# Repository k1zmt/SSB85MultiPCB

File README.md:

# SSB85MultiPCB

Watch it in the work here

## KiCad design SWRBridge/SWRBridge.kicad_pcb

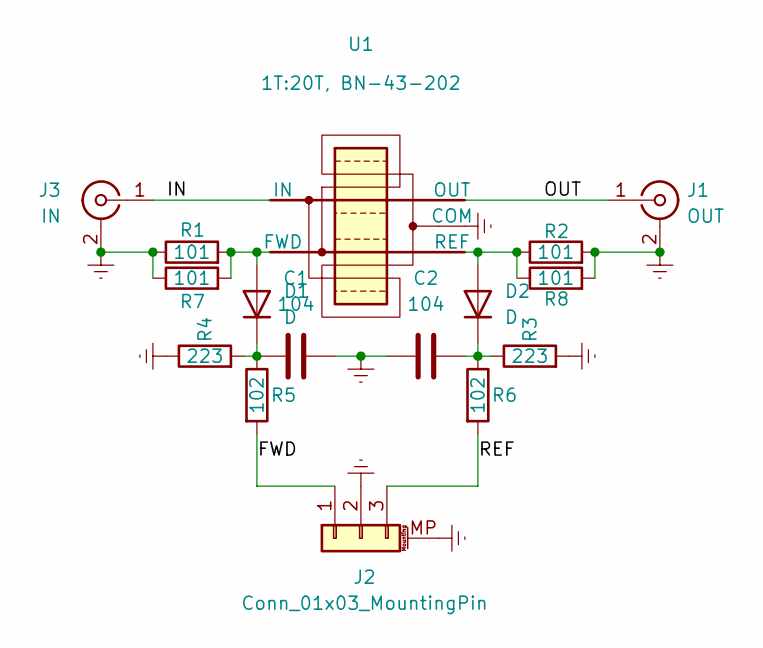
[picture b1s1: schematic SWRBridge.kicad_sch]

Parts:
C1, C2: 104; C_0805_2012Metric
D1, D2: D; D_SOD-123
J1: OUT; SMA_Samtec_SMA-J-P-X-ST-EM1_EdgeMount
J2: Conn_01x03_MountingPin; JST_PH_S3B-PH-SM4-TB_1x03-1MP_P2.00mm_Horizontal
J3: IN; SMA_Samtec_SMA-J-P-X-ST-EM1_EdgeMount
R1, R2, R7, R8: 101; R_1812_4532Metric
R3, R4: 223; R_0805_2012Metric
R5, R6: 102; R_0805_2012Metric
U1: 1T:20T, BN-43-202; Balun_5PIN_BN-43-202_SMD_SWR_Bridge

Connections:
/FWD: J2.1, R5.2
/IN: J3.1 (In), U1.1 (IN)
/OUT: J1.1 (In), U1.2 (OUT)
/REF: J2.3, R6.2
Earth: C1.2, C2.1, J1.2 (Ext), J2.2, J2.MP (MountPin), J3.2 (Ext), R1.1, R2.2, R3.2, R4.1, R7.1, R8.2, U1.3 (COM)
unnamed: D1.2 (A), R1.2, R7.2, U1.5 (FWD)
unnamed: C1.1, D1.1 (K), R4.2, R5.1
unnamed: D2.2 (A), R2.1, R8.1, U1.4 (REF)
unnamed: C2.2, D2.1 (K), R3.1, R6.1

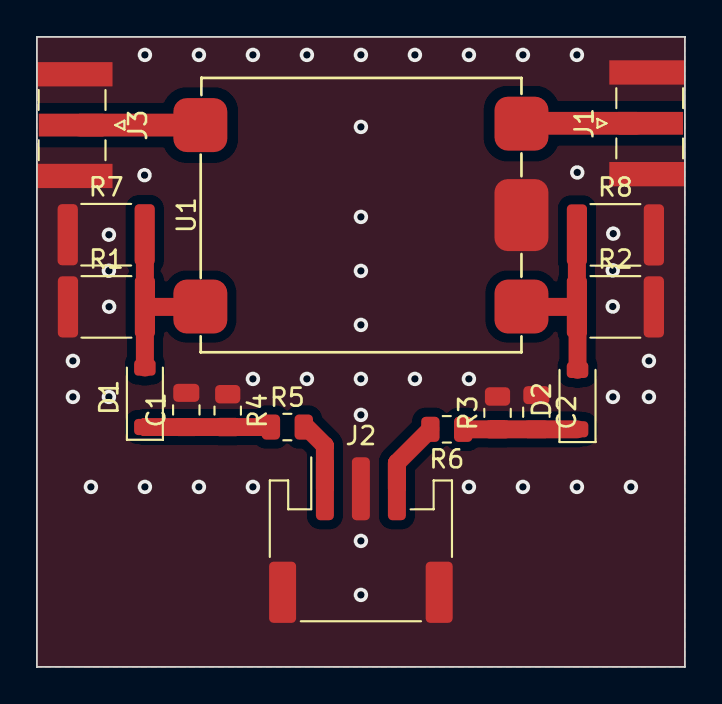
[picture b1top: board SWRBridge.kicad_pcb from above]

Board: 2 copper layers, 36.0 x 35.0 mm, 16 parts (0 on the bottom side), 9 nets.

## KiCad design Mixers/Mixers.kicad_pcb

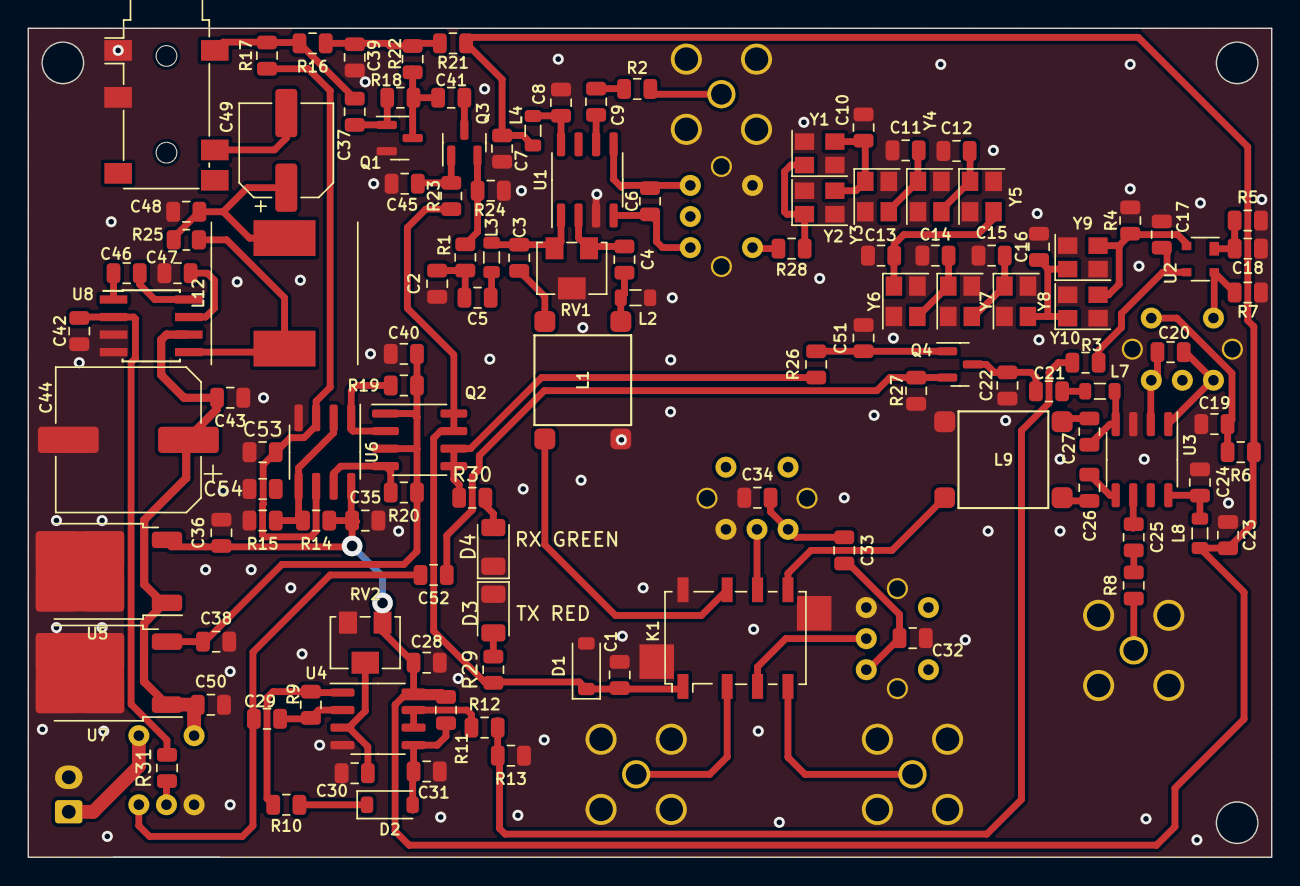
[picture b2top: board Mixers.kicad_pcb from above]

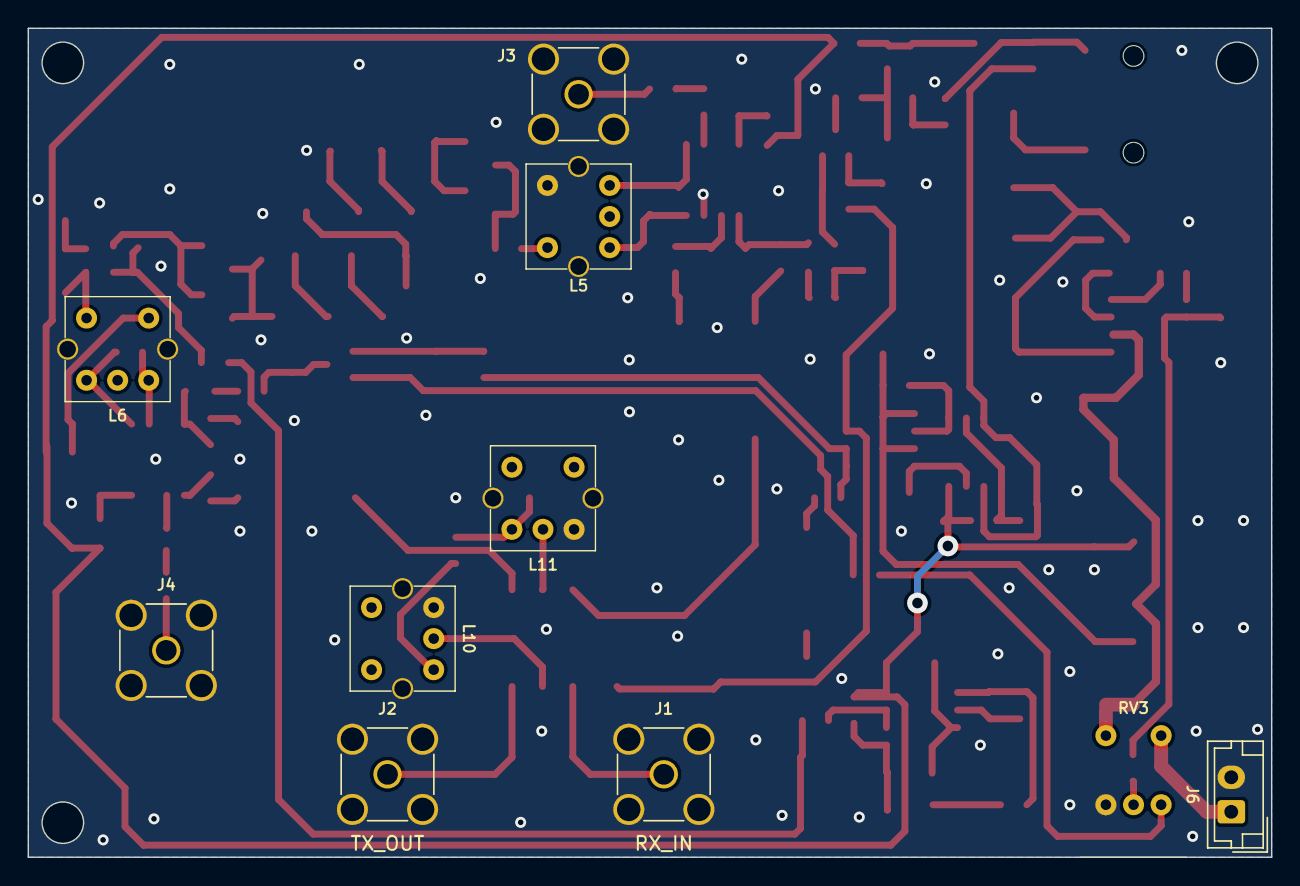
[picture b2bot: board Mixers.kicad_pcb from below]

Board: 2 copper layers, 90.0 x 60.0 mm, 133 parts (10 on the bottom side), 84 nets.

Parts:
C1, C7, C8, C9, C17, C18, C19, C23, C24, C25, C28, C30, C35, C36, C38, C45, C50, C51, C54: 104; C_0805_2012Metric
C2, C3, C22, C26, C27: 103; C_0805_2012Metric
C4, C5, C29, C37, C41: 105; C_0805_2012Metric
C6, C20: 101; C_0805_2012Metric
C10, C11, C12, C13, C14, C15, C16: 330; C_0805_2012Metric
C21, C31, C39, C40, C43, C46, C47, C52: 106; C_0805_2012Metric
C32, C34: 151; C_0805_2012Metric
C33: 270; C_0805_2012Metric
C42: 222; C_0805_2012Metric
C44: 227; CP_Elec_10x12.6
C48: 473; C_0805_2012Metric
C49: 227; CP_Elec_6.3x3
C53: 102; C_0805_2012Metric
D1: 1N4148W; D_SOD-123
D2: MBR0520; D_SOD-123
D3: TX RED; D_1206_3216Metric
D4: RX GREEN; D_1206_3216Metric
J1: RX_IN; SMA_Amphenol_901-144_Vertical
J2: TX_OUT; SMA_Amphenol_901-144_Vertical
J3: VFO1; SMA_Amphenol_901-144_Vertical
J4: VFO2; SMA_Amphenol_901-144_Vertical
J5: AudioJack3_Ground_SwitchTR; Jack_3.5mm_PJ342_Horizontal2
J6: Conn_01x02; JST_EH_B2B-EH-A_1x02_P2.50mm_Vertical
K1: G6K-2F-RF; Relay_DPDT_Omron_G6K-2F-RF
L1, L9: 4T:31T; Balun_BN-43-2402_SMD
L2, L3, L4, L7, L8: 104; L_0805_2012Metric
L5, L6: 9T+9T:7T; L_Coilcraft_Slot7_15
L10, L11: 18T+13T; L_Coilcraft_Slot7_15
L12: L_Ferrite; L_Taiyo-Yuden_NR-10050_9.8x10.0mm
Q1: S9014; SOT-23
Q2: IRF7324; SOIC-8_3.9x4.9mm_P1.27mm
Q3, Q4: BS170F; SOT-23
R1, R16, R24, R27, R31: 103; C_0805_2012Metric
R2, R8: 224; C_0805_2012Metric
R3, R9, R13, R17, R18, R19, R20, R23, R26: 104; C_0805_2012Metric
R4: 471; C_0805_2012Metric
R5: 221; C_0805_2012Metric
R6, R7: 0; C_0805_2012Metric
R10, R12, R21: 102; C_0805_2012Metric
R11, R14: 105; C_0805_2012Metric
R15: 684; C_0805_2012Metric
R22, R29, R30: 472; C_0805_2012Metric
R25: 47R; R_0805_2012Metric
R28: 470; C_0805_2012Metric
RV1, RV2: 503; Potentiometer_Bourns_3224W_Vertical
RV3: R_Potentiometer_Switch; Potentiometer_Switch
U1, U3: SA612; SO-8_3.9x4.9mm_P1.27mm
U2: BF998R; SOT-143R
U4: LM358; SO-8_3.9x4.9mm_P1.27mm
U5: L7808; TO-252-2
U6: LM393; SOIC-8_3.9x4.9mm_P1.27mm
U7: L7805; TO-252-2
U8: LM386; PowerIntegrations_SO-8
Y1, Y2, Y3, Y4, Y5, Y6, Y7, Y8, Y9, Y10: 8MHz; Crystal_SMD_3225-4Pin_3.2x2.5mm

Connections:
+5V: C38.1, C40.1, Q2.1 (S1), Q2.3 (S2), R19.1, R20.1, U7.3 (OUT)
+5V_RX: Q2.5 (D2), Q2.6 (D2), R26.1, R30.1
+5V_TX: C1.2, D1.1 (K), K1.1, Q2.7 (D1), Q2.8 (D1), R23.1, R29.1
+8V: C7.1, C23.1, C28.2, C35.1, C36.1, L4.1, L8.1, R6.1, R11.2, R14.1, R21.1, RV2.1, U4.8 (V+), U5.3 (OUT), U6.8 (V+)
+12V: C43.2, C44.1, C50.1, RV3.5 (S1), U5.1 (IN), U7.1 (IN), U8.6 (V+)
/AGC/AGC_IN: C29.1, C52.2, RV3.3
/AGC/AGC_OUT: R3.1, R12.2, R13.2
/Band Pass Filter/BPF_IN: K1.3, L10.2
/Band Pass Filter/BPF_OUT: K1.6, L11.2
/Intermediate Frequency Filter/IF_IN: R28.2, Y1.1, Y2.1
/Intermediate Frequency Filter/IF_OUT: R4.1, U2.4 (G1), Y9.3, Y10.3
/Microphone + Audio Amplifier/MIC_OUT: Q3.2 (S), R1.1, R24.1
/Mixer1/MX1_RF_IN: K1.7, L1.1
/Mixer2/MX2_OUT_TX: K1.5, L9.2
Earth: C1.1, C2.1, C7.2, C8.2, C10.1, C11.1, C12.1, C13.1, C14.1, C15.1, C16.1, C17.1, C18.1, C19.1, C22.1, C23.2, C24.2, C28.1, C30.1, C31.1, C32.1, C34.1, C35.2, C36.2, C38.2, C39.2, C40.2, C42.2, C43.1, C44.2, C45.2, C47.1, C48.2, C50.2, C51.2, C53.2, C54.2, D1.2 (A), D3.1 (K), D4.1 (K), J1.2 (Ext), J2.2 (Ext), J3.2 (Ext), J4.2 (Ext), J5.G, J5.R, J6.2, K1.8, K1.9, L1.2, L2.2, L5.4, L5.MP, L6.MP, L9.1, L10.3, L10.MP, L11.3, L11.MP, Q1.2 (E), R4.2, R5.2, R7.2, R13.1, R15.2, R24.2, R27.2, RV1.2, RV2.3, RV3.1, U1.3 (GND), U3.3 (GND), U4.4 (V-), U5.2 (GND), U6.4 (V-), U7.2 (GND), U8.3 (+), U8.4 (GND), Y1.2, Y1.4, Y2.2, Y2.4, Y3.2, Y3.4, Y4.2, Y4.4, Y5.2, Y5.4, Y6.2, Y6.4, Y7.2, Y7.4, Y8.2, Y8.4, Y9.2, Y9.4, Y10.2, Y10.4
unnamed: C2.2, C5.1, R1.2
unnamed: C3.1, L1.4
unnamed: C4.1, L1.3, L2.1
unnamed: C5.2, L3.1
unnamed: C9.2, R2.2
unnamed: C10.2, Y1.3, Y2.3, Y3.1
unnamed: C11.2, Y3.3, Y4.1
unnamed: C12.2, Y4.3, Y5.1
unnamed: C13.2, Y5.3, Y6.1
unnamed: C14.2, Y6.3, Y7.1
unnamed: C15.2, Y7.3, Y8.1
unnamed: C16.2, Y8.3, Y9.1, Y10.1
unnamed: C19.2, L6.4, R6.2
unnamed: C21.1, L7.1
unnamed: C25.2, R8.2
unnamed: C26.2, L9.3
unnamed: C27.2, L9.4
unnamed: C32.2, C33.2, L10.1
unnamed: C33.1, C34.2, L11.1
unnamed: C37.2, J5.S, R16.2, R17.1
unnamed: C39.1, R16.1, R21.2, R22.1
unnamed: C46.1, U8.1 (GAIN)
unnamed: C46.2, U8.8 (GAIN)
unnamed: C48.1, C49.1, L12.2, R25.2
unnamed: C31.2, D2.2 (A), R11.1, U4.5 (+)
unnamed: D2.1 (K), R10.2
unnamed: D3.2 (A), R29.2
unnamed: D4.2 (A), R30.2
unnamed: J1.1 (In), K1.2
unnamed: J2.1 (In), K1.4
unnamed: J3.1 (In), R2.1
unnamed: J4.1 (In), R8.1
unnamed: J6.1, RV3.4 (S2)
unnamed: L5.5, R28.1
unnamed: L12.1, R25.1, U8.5
unnamed: C37.1, Q1.1 (B), R18.2
unnamed: C41.2, Q1.3 (C), R18.1, R22.2
unnamed: Q2.2 (G1), R19.2, U6.1
unnamed: Q2.4 (G2), R20.2, U6.7
unnamed: C41.1, Q3.3 (D)
unnamed: C45.1, Q3.1 (G), R23.2
unnamed: C21.2, C22.2, Q4.3 (D)
unnamed: C51.1, Q4.1 (G), R26.2
unnamed: C52.1, Q4.2 (S), R27.1
unnamed: R9.2, R10.1, U4.1
unnamed: R31.1, RV3.2
unnamed: C3.2, L3.2, RV1.3, U1.1 (IN_A)
unnamed: C4.2, RV1.1, U1.2 (IN_B)
unnamed: C9.1, U1.6 (OSC_B)
unnamed: C6.1, L5.1, U1.4 (OUT_A)
unnamed: C6.2, L5.3, U1.5 (OUT_B)
unnamed: C8.1, L4.2, U1.8 (Vcc)
unnamed: L6.5, R7.1, U2.2 (D)
unnamed: C17.2, R3.2, U2.3 (G2)
unnamed: C18.2, R5.1, U2.1 (S)
unnamed: C20.2, L6.1, U3.1 (IN_A)
unnamed: C20.1, L6.3, U3.2 (IN_B)
unnamed: C25.1, U3.6 (OSC_B)
unnamed: C27.1, L7.2, U3.4 (OUT_A)
unnamed: C26.1, U3.5 (OUT_B)
unnamed: C24.1, L8.2, U3.8 (Vcc)
unnamed: C30.2, RV2.2, U4.3 (+)
unnamed: C29.2, R9.1, U4.2 (-)
unnamed: R12.1, U4.6 (-), U4.7
unnamed: C53.1, R17.2, U6.3 (+), U6.6 (-)
unnamed: C54.1, R14.2, R15.1, U6.2 (-), U6.5 (+)
unnamed: C42.1, R31.2, U8.2 (-)
unnamed: C47.2, U8.7 (BYPASS)
SPK_OUT: C49.2, J5.T

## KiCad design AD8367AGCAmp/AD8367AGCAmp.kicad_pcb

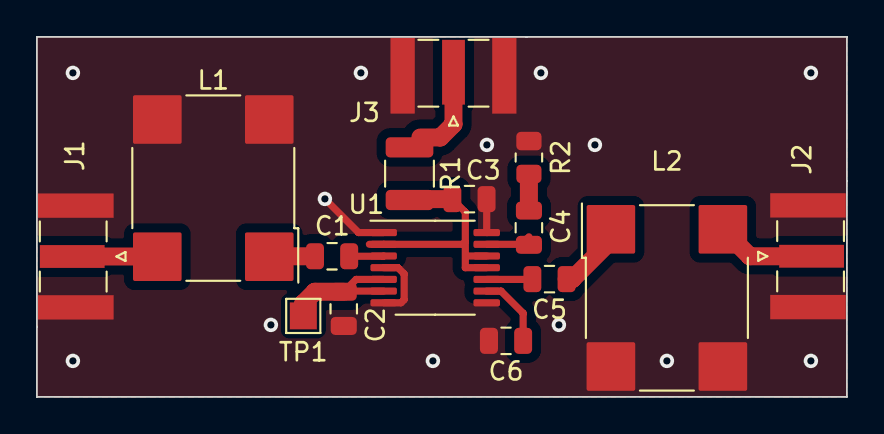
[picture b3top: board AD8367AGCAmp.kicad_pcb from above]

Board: 2 copper layers, 45.0 x 20.0 mm, 15 parts (0 on the bottom side), 13 nets.

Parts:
C1, C3, C5: 104; C_0805_2012Metric
C2: 105*; C_0805_2012Metric
C4, C6: 103*; C_0805_2012Metric
J1: IF_IN; SMA_Samtec_SMA-J-P-X-ST-EM1_EdgeMount
J2: IF_OUT; SMA_Samtec_SMA-J-P-X-ST-EM1_EdgeMount
J3: +5V; SMA_Samtec_SMA-J-P-X-ST-EM1_EdgeMount
L1: 2:1; L_CommonModeChoke_Wuerth_WE-SL5
L2: Z 4:1; L_CommonModeChoke_Wuerth_WE-SL5
R1: 0; R_1210_3225Metric
R2: 101*; R_0805_2012Metric
TP1: TestPoint; TestPoint_Pad_1.5x1.5mm
U1: AD8367ARU; TSSOP-14_4.4x5mm_P0.65mm

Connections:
+5V: J3.1 (In), R1.1
Earth: C2.2, C3.1, C6.2, J1.2 (Ext), J2.2 (Ext), J3.2 (Ext), L1.2, L1.3, L2.2, L2.3, R2.2, U1.1 (ICOM), U1.4 (MODE), U1.7 (ICOM), U1.8 (OCOM), U1.14 (ICOM)
unnamed: C1.2, L1.1
unnamed: C4.2, R2.1
unnamed: C5.1, L2.1
unnamed: J1.1 (In), L1.4
unnamed: J2.1 (In), L2.4
unnamed: C6.1, U1.9 (DECL)
unnamed: C2.1, TP1.1, U1.5 (GAIN), U1.6 (DETO)
unnamed: C3.2, R1.2, U1.2 (EN), U1.11 (VPSO), U1.12 (VPSI)
unnamed: C4.1, U1.13 (HPFL)
unnamed: C1.1, U1.3 (INPUT)
unnamed: C5.2, U1.10 (OUTPUT)

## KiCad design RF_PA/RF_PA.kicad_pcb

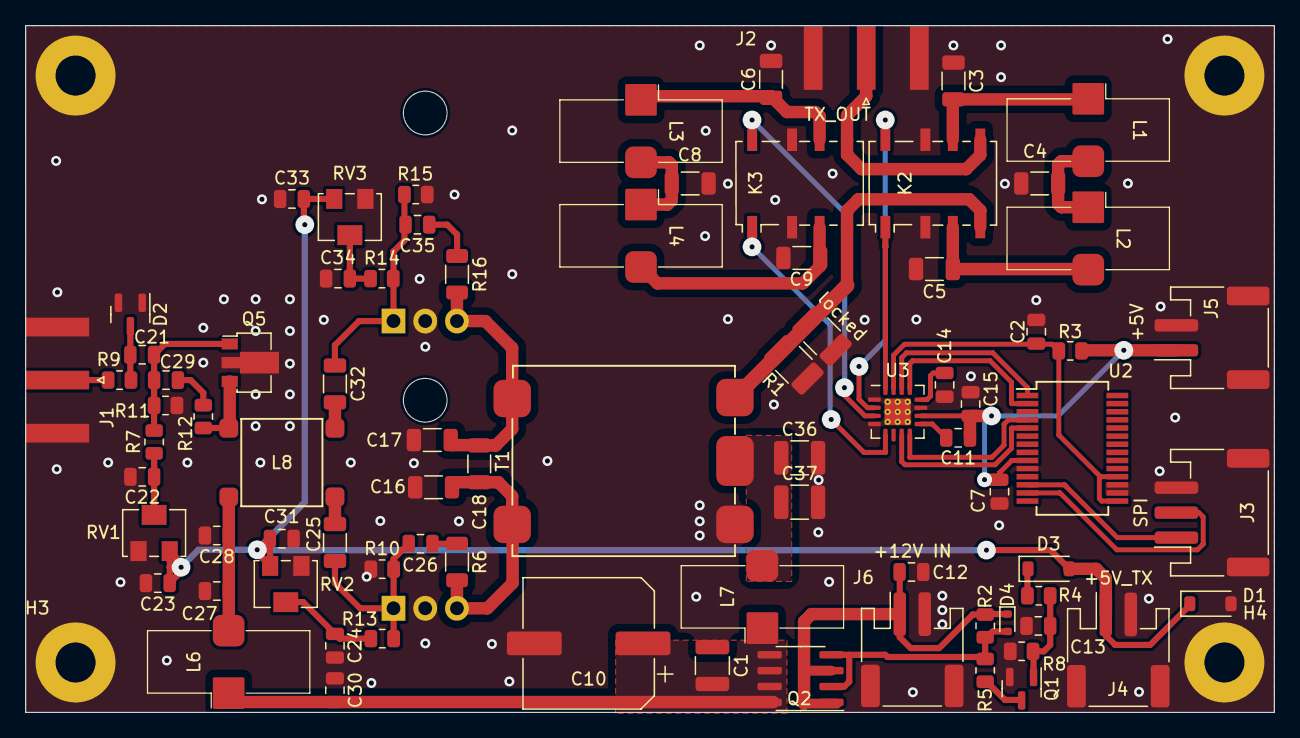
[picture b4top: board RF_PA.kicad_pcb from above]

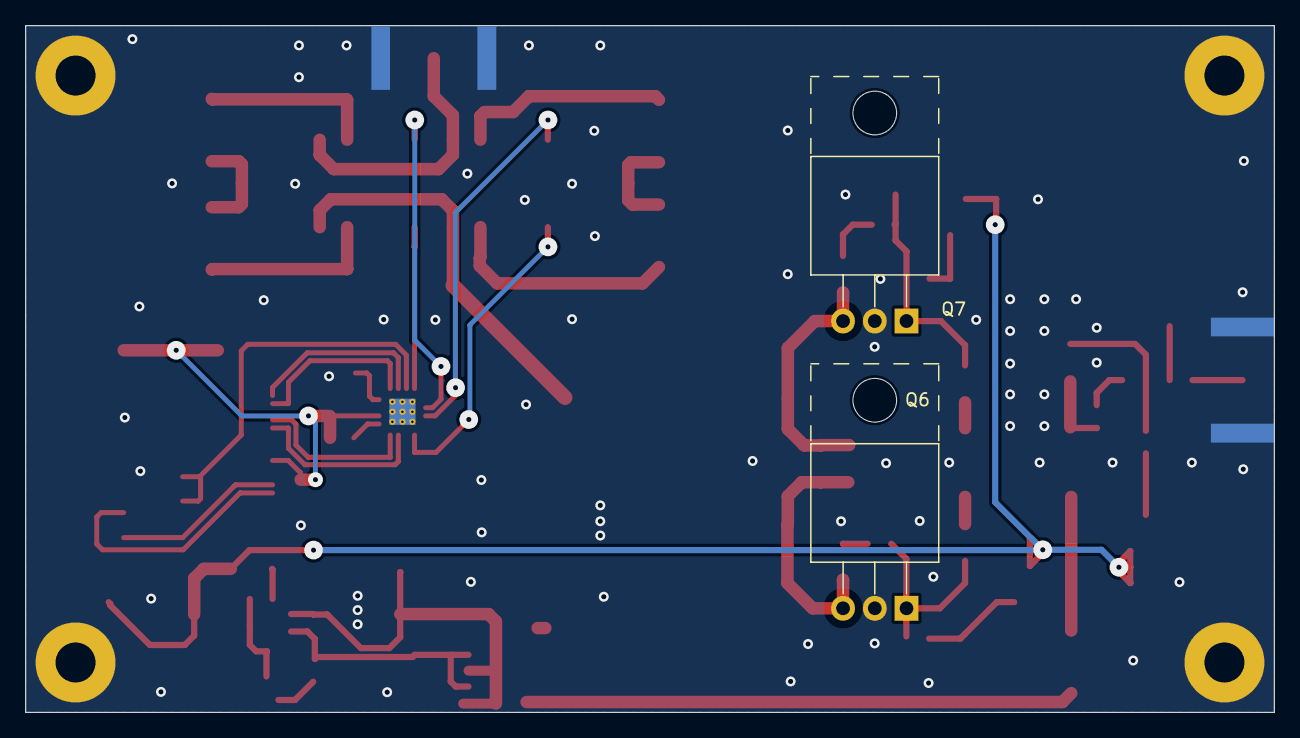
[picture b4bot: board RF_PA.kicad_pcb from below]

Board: 2 copper layers, 100.0 x 55.0 mm, 86 parts (2 on the bottom side), 48 nets.

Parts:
C1, C37: 104; C_1210_3225Metric
C2, C7, C11, C12, C15, C21, C22, C23, C24, C27, C28, C30, C31, C33, C34: 104; C_0805_2012Metric
C3, C5: 102; C_1206_3216Metric
C4: 152; C_1206_3216Metric
C6, C9: 100p; C_1206_3216Metric
C8: 220p; C_1206_3216Metric
C10: 1000uFx16V; CP_Elec_10x12.6
C13, C14: 106; C_0805_2012Metric
C16, C17: 561; C_1206_3216Metric
C18: 331; C_1206_3216Metric
C25, C32: 104; C_1206_3216Metric
C26, C35: 223; C_0805_2012Metric
C29: 103; C_0805_2012Metric
C36: 223; C_1210_3225Metric
D1, D3: 1N4148W; D_SOD-123
D2: BAV99; SOT-23
D4: DZ2S100X0L; D_SOD-523
H1, H2, H3, H4: MH; MountingHole_3.2mm_M3_Pad
J1: TX_IN; SMA_Amphenol_132289_EdgeMount
J2: TX_OUT; SMA_Amphenol_132289_EdgeMount
J3: SPI; JST_PH_S3B-PH-SM4-TB_1x03-1MP_P2.00mm_Horizontal
J4: +5V_TX; JST_PH_S2B-PH-SM4-TB_1x02-1MP_P2.00mm_Horizontal
J5: +5V; JST_PH_S2B-PH-SM4-TB_1x02-1MP_P2.00mm_Horizontal
J6: +12V IN; JST_PH_S2B-PH-SM4-TB_1x02-1MP_P2.00mm_Horizontal
K2, K3: G6KU-2; Relay_DPDT_Omron_G6K-2F-Y
L1: 2.2uH; L_T50_L13_W8_P5mm
L2: T50-2, 21t; L_T50_L13_W8_P5mm
L3: 330nHn; L_T50_L13_W8_P5mm
L4: 330n, T50-6, 9t; L_T50_L13_W8_P5mm
L6: 10T; L_T50_L13_W8_P5mm
L7: T50-2, 15T, d0.5; L_T50_L13_W8_P5mm
L8: 1:3; Balun_BN-43-2402_SMD
Q1: BSS138; SOT-23
Q2: IRF7324; SOIC-8_3.9x4.9mm_P1.27mm
Q5: RD01MUS2B; SOT-89-3
Q6, Q7: RD16HHF1; TO-220-3_Horizontal_TabUp
R1: 511; R_1210_3225Metric_Pad1.30x2.65mm_HandSolder
R2, R3, R4: 103; R_0805_2012Metric
R5: 102; R_0805_2012Metric
R6, R16: 751; R_1206_3216Metric
R7, R13, R14: 331; R_0805_2012Metric
R8: 475; R_0805_2012Metric
R9: 47R; R_0805_2012Metric
R10, R11, R15: 472; R_0805_2012Metric
R12: 681; R_0805_2012Metric
RV1, RV2, RV3: 502; Potentiometer_Bourns_3214W_Vertical
T1: 0.5+0.5T:4T; Balun_5PIN_BN-43-202_SMD_Inverse
U2: MCP23017_SS; SSOP-28_5.3x10.2mm_P0.65mm
U3: DRV8833RTY; Texas_S-PWQFN-N16_EP2.1x2.1mm_ThermalVias
locked: 511; R_1210_3225Metric_Pad1.30x2.65mm_HandSolder

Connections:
+5V: C7.1, C11.2, C15.2, J5.1, R3.1, U2.9 (VDD), U3.10 (VM)
+5V_TX: C23.1, C31.2, C33.2, D1.1 (K), D3.2 (A), J4.1, RV1.3, RV2.3, RV3.3
+12V_TX: C1.2, C10.1, C30.1, L6.1, L7.1, Q2.5 (D2), Q2.6 (D2), Q2.7 (D1), Q2.8 (D1)
/DRNP: C36.2, C37.1, L7.2, T1.2 (PM)
/DRN_1: C16.2, C18.1, Q6.3 (D), R6.2, T1.1 (PR1)
/DRN_2: C17.2, C18.2, Q7.3 (D), R16.2, T1.3 (PR2)
/FLT4M_1: C3.2, K2.6, L1.1
/FLT4M_2: C4.2, L1.2, L2.1
/FLT4M_3: C5.2, K2.3, L2.2
/FLT30M_1: C6.2, K3.6, L3.1
/FLT30M_2: C8.2, L3.2, L4.1
/FLT30M_3: C9.2, K3.3, L4.2
/FLT_IN: K2.4, K3.4, R1.1, T1.4 (S1), locked.1
/FLT_OUT: J2.1 (In), K2.5, K3.5
/R10M: K3.8, U3.3 (BOUT2)
/R80M: K2.8, U3.2 (AOUT2)
/R_10M: U2.4 (GPB3), U3.8 (BIN2)
/R_80M: U2.2 (GPB1), U3.13 (AIN2)
/S10M: K3.1, U3.5 (BOUT1)
/S80M: K2.1, U3.16 (AOUT1)
/S_10M: U2.5 (GPB4), U3.7 (BIN1)
/S_80M: U2.1 (GPB0), U3.14 (AIN1)
Earth: C1.1, C2.1, C3.1, C4.1, C5.1, C6.1, C7.2, C8.1, C9.1, C10.2, C12.1, C13.2, C14.1, C15.1, C16.1, C17.1, C22.2, C23.2, C24.1, C27.2, C28.2, C30.2, C31.1, C33.1, C34.1, C36.1, C37.2, D1.2 (A), D2.1 (K), D2.2 (A), H1.1, H2.1, H3.1, H4.1, J1.2 (Ext), J2.2 (Ext), J3.3, J3.MP (MountPin), J4.2, J4.MP (MountPin), J5.2, J5.MP (MountPin), J6.2, J6.MP (MountPin), K2.2, K2.7, K3.2, K3.7, Q1.2 (S), Q5.2 (S), Q6.2 (S), Q7.2 (S), R1.2, R8.2, R10.1, R11.1, R15.1, RV1.1, RV2.1, RV3.1, T1.5 (S2), U2.10 (VSS), U2.16 (A1), U2.17 (A2), U3.1 (AISEN), U3.4 (BISEN), U3.11 (GND), U3.17 (GND(PPAD)), locked.2
unnamed: C21.2, D2.3 (K), R9.2
unnamed: C22.1, R7.1, RV1.2
unnamed: C24.2, R13.1, RV2.2
unnamed: C25.2, L8.3
unnamed: C26.1, R6.1
unnamed: C27.1, C28.1, L6.2, L8.2
unnamed: C29.1, R12.1
unnamed: C32.2, L8.4
unnamed: C34.2, R14.1, RV3.2
unnamed: C35.1, R16.1
unnamed: D3.1 (K), R4.2
unnamed: D4.2 (A), Q2.2 (G1), Q2.4 (G2), R2.2, R5.2
unnamed: C12.2, D4.1 (K), J6.1, Q2.1 (S1), Q2.3 (S2), R2.1
unnamed: J1.1 (In), R9.1
unnamed: Q1.3 (D), R5.1
unnamed: C13.1, Q1.1 (G), R4.1, R8.1
unnamed: L8.1, Q5.3 (D), R12.2
unnamed: C21.1, C29.2, Q5.1 (G), R7.2, R11.2
unnamed: C25.1, C26.2, Q6.1 (G), R10.2, R13.2
unnamed: C32.1, C35.2, Q7.1 (G), R14.2, R15.2
unnamed: C2.2, R3.2, U2.15 (A0), U2.18 (~RESET), U3.15 (nSLEEP)
unnamed: C11.1, U3.9 (VCP)
unnamed: C14.2, U3.12 (VINT)
SCL: J3.1, U2.12 (SCK)
SDA: J3.2, U2.13 (SDA)

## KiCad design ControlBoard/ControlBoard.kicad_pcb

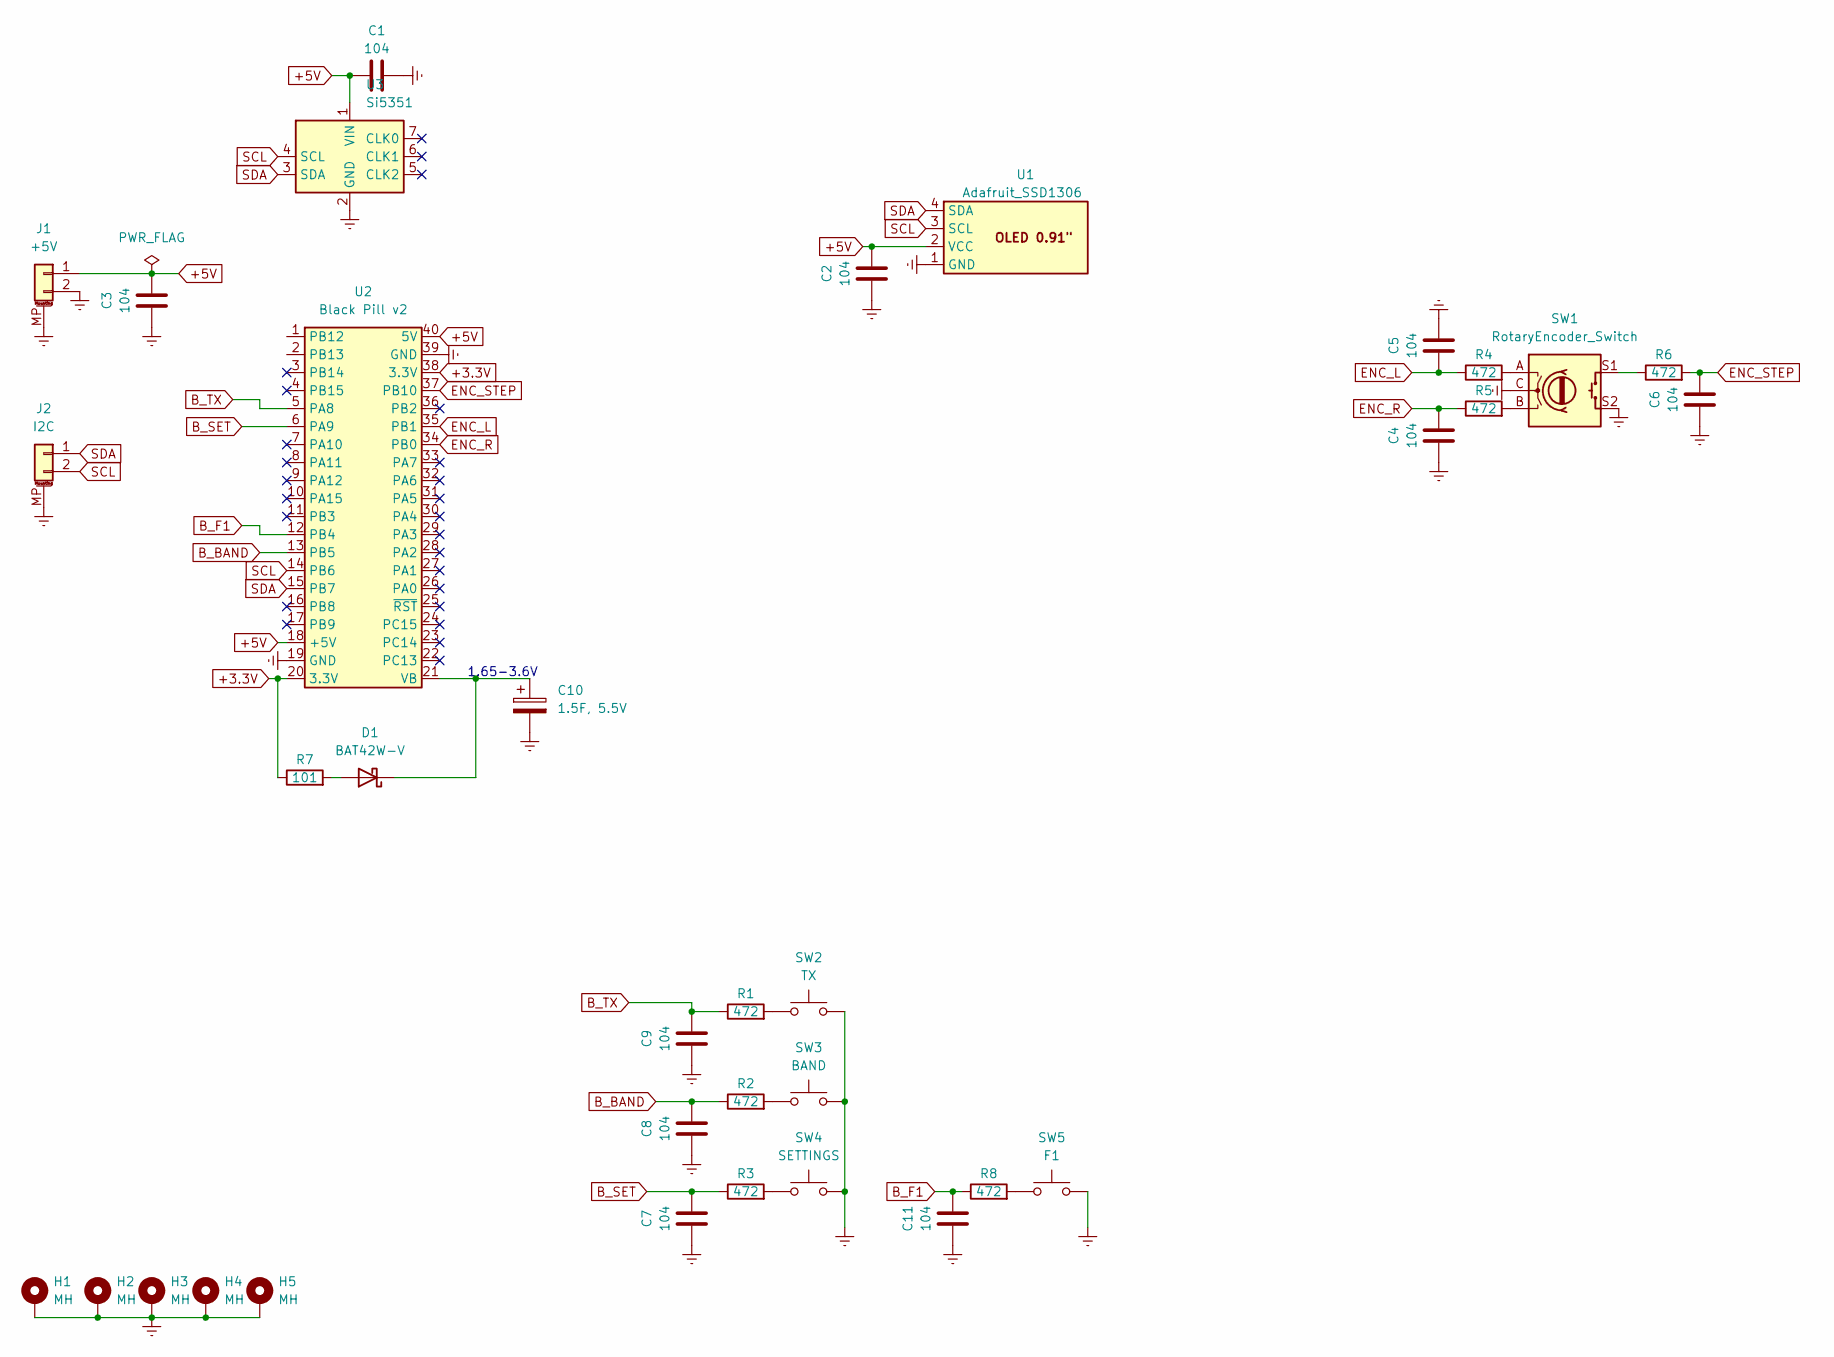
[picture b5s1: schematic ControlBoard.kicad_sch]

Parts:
C1, C2, C3, C4, C5, C6, C7, C8, C9, C11: 104; C_0805_2012Metric
C10: 1.5F, 5.5V; Supercapacitor_C_D21_H7.5_P5.0
D1: BAT42W-V; D_SOD-123
H1, H2, H3, H4, H5: MH; MountingHole_3.2mm_M3_Pad
J1: +5V; JST_PH_S2B-PH-SM4-TB_1x02-1MP_P2.00mm_Horizontal
J2: I2C; JST_PH_S2B-PH-SM4-TB_1x02-1MP_P2.00mm_Horizontal
R1, R2, R3, R4, R5, R6, R8: 472; R_0805_2012Metric
R7: 101; R_0805_2012Metric
SW1: RotaryEncoder_Switch; RotaryEncoder_Alps_EC11E-Switch_Vertical_H20mm
SW2: TX; SW_SPST_PTS645
SW3: BAND; SW_SPST_PTS645
SW4: SETTINGS; SW_SPST_PTS645
SW5: F1; SW_SPST_PTS645
U1: Adafruit_SSD1306; Module_OLED_091
U2: Black Pill v2; Module_BlackPill_v2
U3: Si5351; Module_Si5351

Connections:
+3.3V: R7.1, U2.20 (3.3V), U2.38 (3.3V)
+5V: C1.1, C2.2, C3.2, J1.1, U1.2 (VCC), U2.18 (+5V), U2.40 (5V), U3.1 (VIN)
B_BAND: C8.2, R2.1, U2.13 (PB5)
B_F1: C11.2, R8.1, U2.12 (PB4)
B_SET: C7.2, R3.1, U2.6 (PA9)
B_TX: C9.2, R1.1, U2.5 (PA8)
ENC_L: C5.1, R4.1, U2.35 (PB1)
ENC_R: C4.2, R5.1, U2.34 (PB0)
ENC_STEP: C6.2, R6.2, U2.37 (PB10)
Earth: C1.2, C2.1, C3.1, C4.1, C5.2, C6.1, C7.1, C8.1, C9.1, C10.2, C11.1, H1.1, H2.1, H3.1, H4.1, H5.1, J1.2, J1.MP (MountPin), J2.MP (MountPin), SW1.C, SW1.S2, SW2.2, SW3.2, SW4.2, SW5.2, U1.1 (GND), U2.19 (GND), U2.39 (GND), U3.2 (GND)
unnamed: D1.2 (A), R7.2
unnamed: C10.1, D1.1 (K), U2.21 (VB)
unnamed: R1.2, SW2.1
unnamed: R2.2, SW3.1
unnamed: R3.2, SW4.1
unnamed: R4.2, SW1.A
unnamed: R5.2, SW1.B
unnamed: R6.1, SW1.S1
unnamed: R8.2, SW5.1
SCL: J2.2, U1.3 (SCL), U2.14 (PB6), U3.4 (SCL)
SDA: J2.1, U1.4 (SDA), U2.15 (PB7), U3.3 (SDA)

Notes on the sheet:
1.65-3.6V

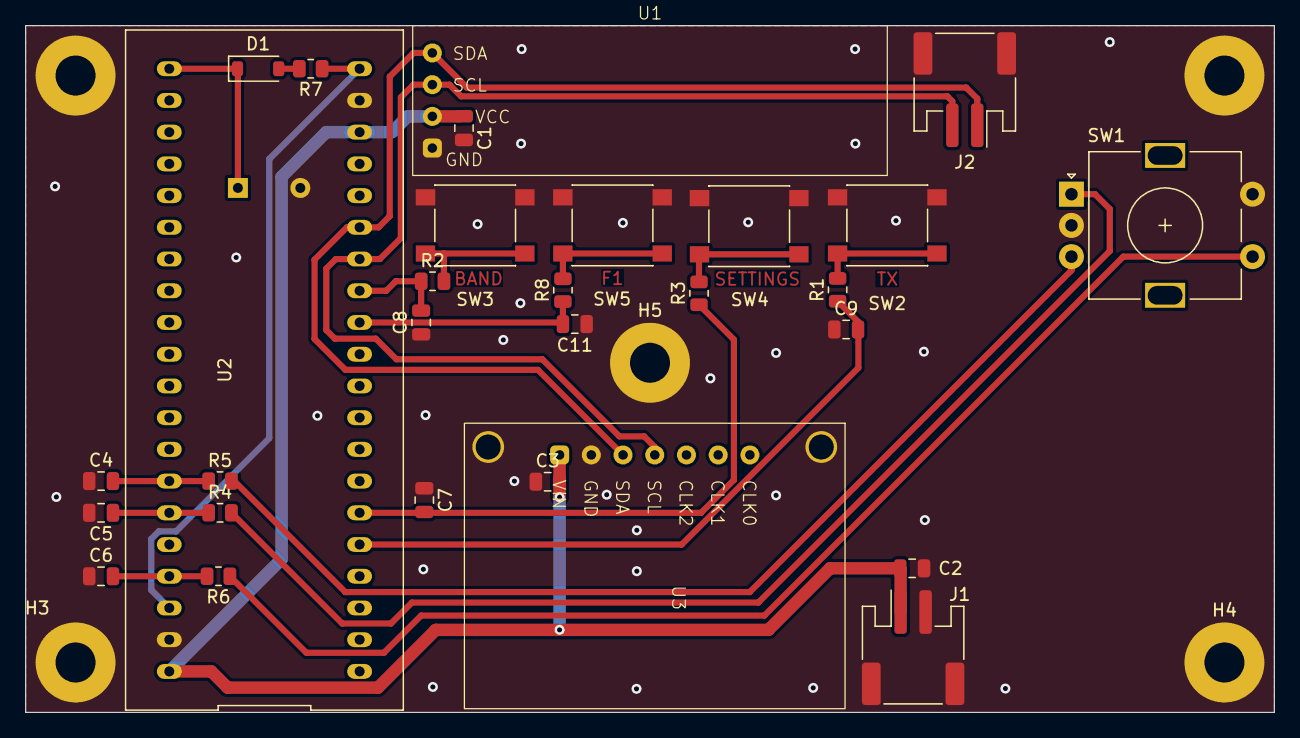
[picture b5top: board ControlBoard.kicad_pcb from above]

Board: 2 copper layers, 100.0 x 55.0 mm, 35 parts (1 on the bottom side), 21 nets.

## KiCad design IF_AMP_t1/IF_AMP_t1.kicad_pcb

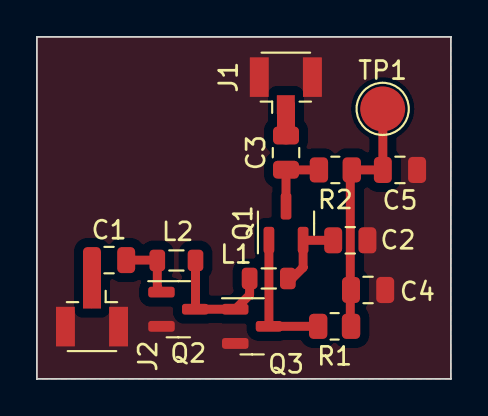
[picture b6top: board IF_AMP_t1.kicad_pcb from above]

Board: 2 copper layers, 23.0 x 19.0 mm, 15 parts (0 on the bottom side), 9 nets.

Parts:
C1, C2, C3, C4, C5: 104; C_0805_2012Metric
J1, J2: Conn_Coaxial; U.FL_Hirose_U.FL-R-SMT-1_Vertical
L1, L2: 104; L_0805_2012Metric
Q1, Q2, Q3: BC848; SOT-23
R1: 512; R_0805_2012Metric
R2: 152; R_0805_2012Metric
TP1: TestPoint; TestPoint_Pad_D2.5mm

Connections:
Earth: C2.2, C4.1, C5.1, J1.2 (Ext), J2.2 (Ext), Q2.2 (E), Q3.2 (E)
unnamed: C4.2, C5.2, R1.1, R2.1, TP1.1
unnamed: C3.2, J1.1 (In)
unnamed: C1.1, J2.1 (In)
unnamed: Q1.1 (B), Q3.3 (C), R1.2
unnamed: C3.1, Q1.3 (C), R2.2
unnamed: C2.1, L1.1, Q1.2 (E)
unnamed: C1.2, L2.2, Q2.1 (B)
unnamed: L1.2, L2.1, Q2.3 (C), Q3.1 (B)

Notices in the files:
AD831HotBoard/AD831HotBoard.kicad_pcb:
(c) 2023 Philipp Tkachev
